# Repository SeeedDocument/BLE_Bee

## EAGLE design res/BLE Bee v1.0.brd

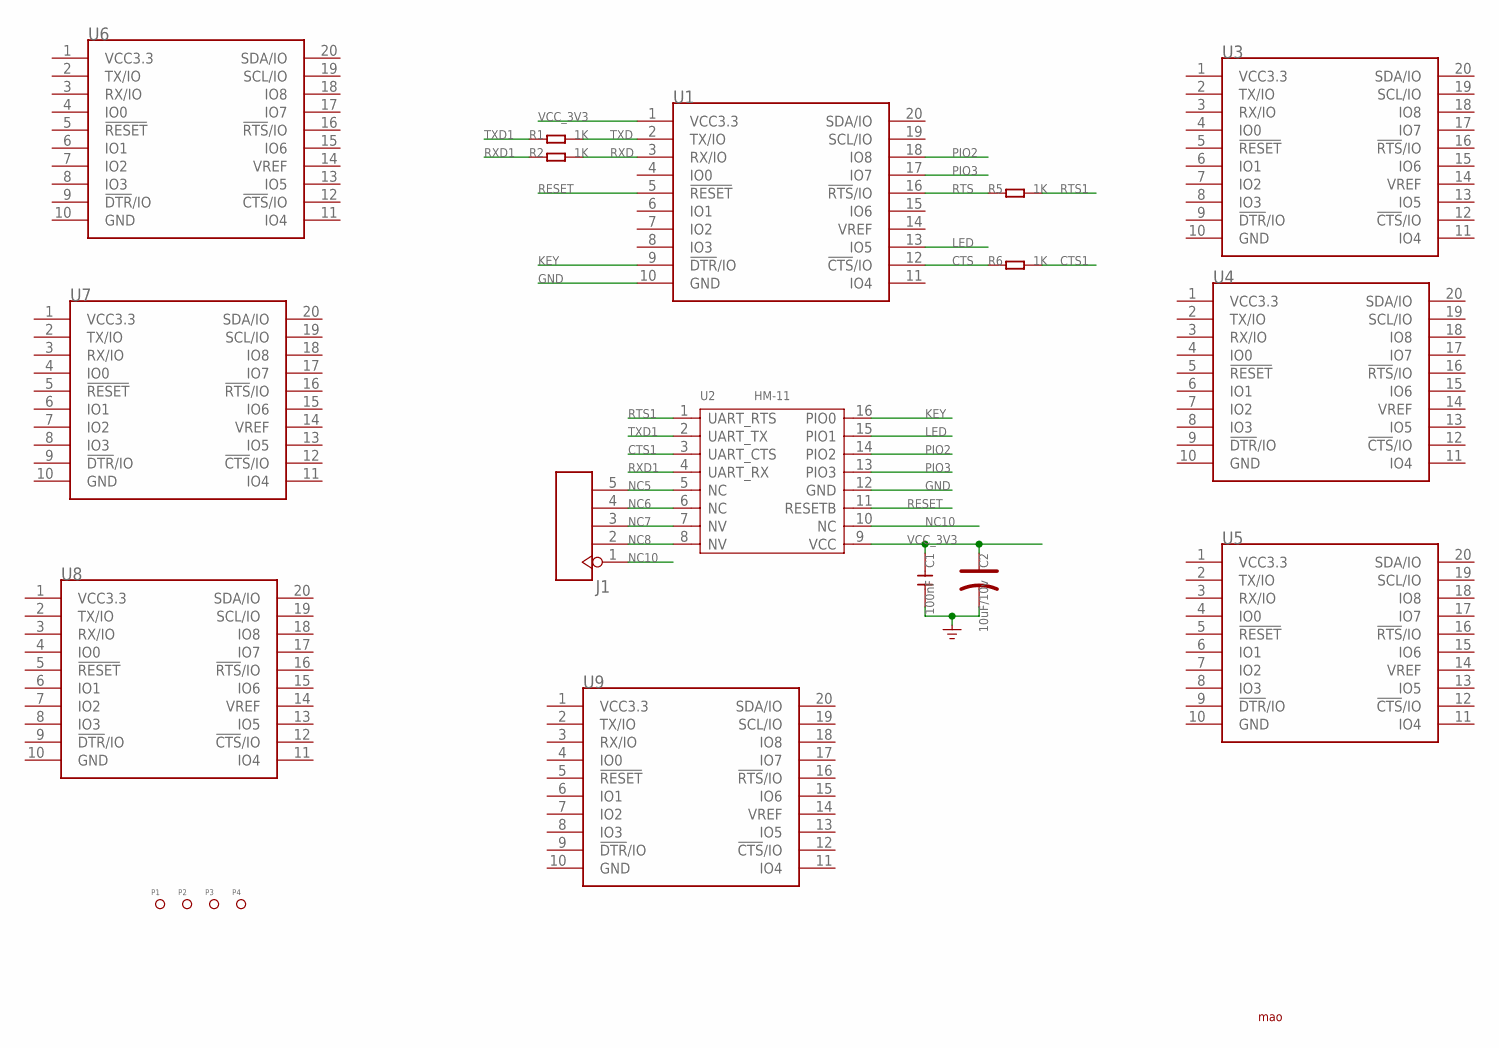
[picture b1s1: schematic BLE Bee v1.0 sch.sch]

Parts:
C1: 100nF; C0603
C2: 10uF/10v; AVX-A
J1: HEADER-5P-2.0; 5P-2.0
P1, P2, P3, P4: PAD-MARK; ROUND-MARK-1.0
R1, R2, R5, R6: 1K; R0603
U1, U3, U4, U5, U6, U7, U8, U9: BEE-OPENBEE-DIP; 20P-DIP-2.0
U2: HM-11; 16P-18.5X13.5X0.8

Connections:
CTS: R6.1, U1.12 (!CTS!/IO)
CTS1: R6.2, U2.3 (UART_CTS)
GND: C1.2, C2.-, U1.10 (GND), U2.12 (GND)
KEY: U1.9 (!DTR!/IO), U2.16 (PIO0)
LED: U1.13 (IO5), U2.15 (PIO1)
NC5: J1.5, U2.5 (NC)
NC6: J1.4, U2.6 (NC)
NC7: J1.3, U2.7 (NV)
NC8: J1.2, U2.8 (NV)
NC10: J1.1, U2.10 (NC)
PIO2: U1.18 (IO8), U2.14 (PIO2)
PIO3: U1.17 (IO7), U2.13 (PIO3)
RESET: U1.5 (!RESET), U2.11 (RESETB)
RTS: R5.1, U1.16 (!RTS!/IO)
RTS1: R5.2, U2.1 (UART_RTS)
RXD: R2.2, U1.3 (RX/IO)
RXD1: R2.1, U2.4 (UART_RX)
TXD: R1.2, U1.2 (TX/IO)
TXD1: R1.1, U2.2 (UART_TX)
VCC_3V3: C1.1, C2.+, U1.1 (VCC3.3), U2.9 (VCC)

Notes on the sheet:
mao

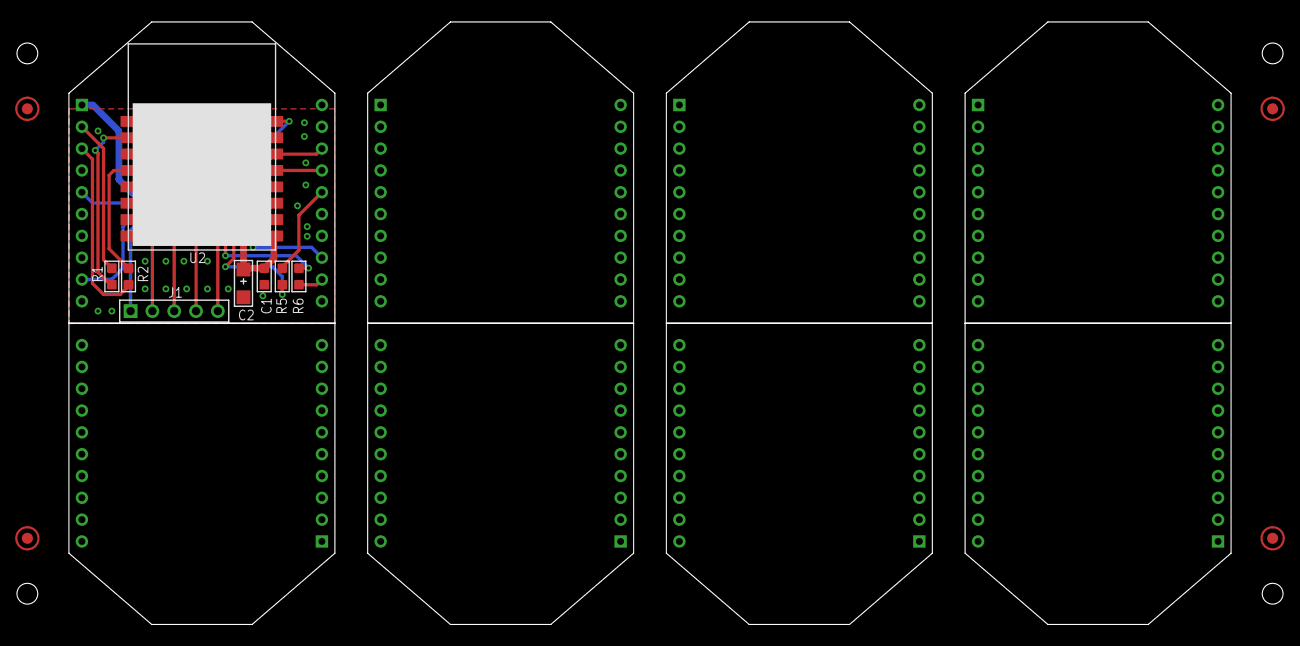
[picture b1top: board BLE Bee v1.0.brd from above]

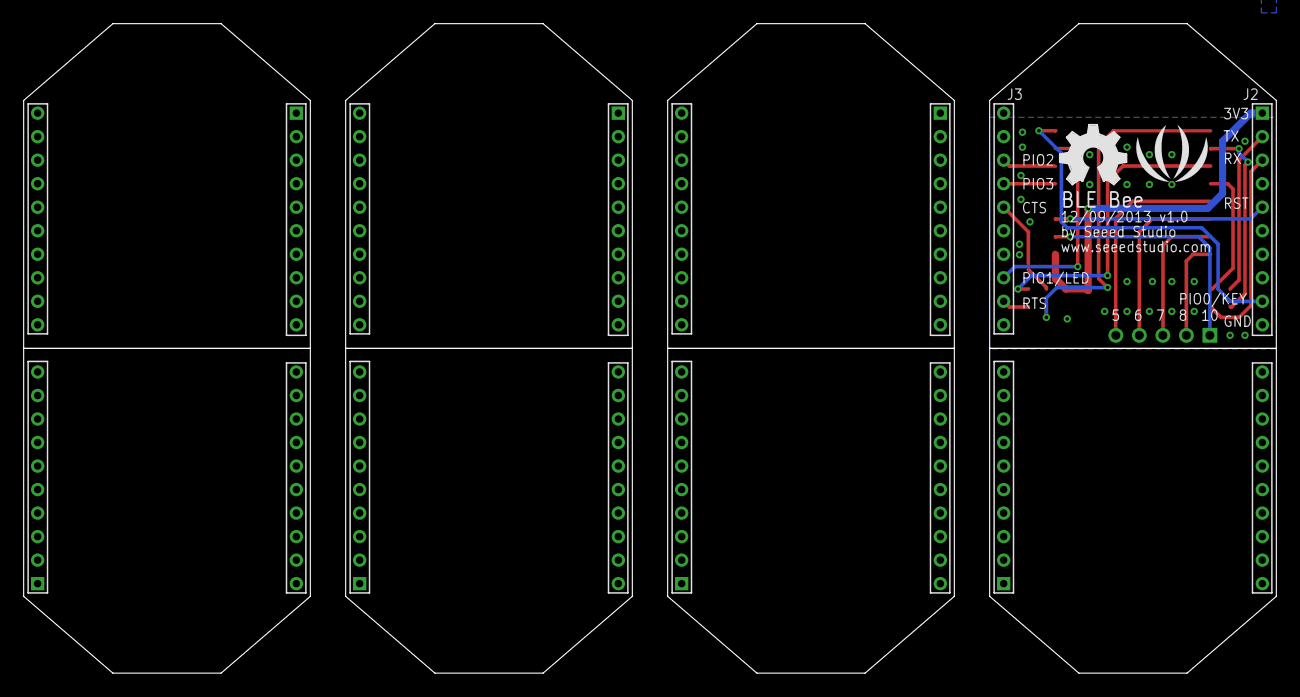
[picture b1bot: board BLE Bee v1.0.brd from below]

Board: 2 copper layers, 106.5 x 55.2 mm, 22 parts (2 on the bottom side), 20 nets.

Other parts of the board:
U$2: LOGO_SILK
U$3: OSHW_FILLX200_NOTEXT

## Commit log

2017-05-20 upgrade
2019-11-05 add
    add
